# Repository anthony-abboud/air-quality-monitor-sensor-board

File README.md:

# AirQualityMonitor-SensorBoard (Pico2JSTboard)

Custom PCB for Lehigh University's Sustainable Engineering Club Air Quality Monitor project. Integrates a Raspberry Pi Pico 2 W with a Sensirion SEN54 environmental sensor for low-cost, IoT-connected indoor air quality monitoring.

## Overview

The original prototype connected the Pico 2 W to the SEN54 sensor via breadboard and loose cabling. This board replaces that setup with a compact, pluggable assembly: two socket headers accept the Pico 2 W directly, and an onboard JST connector interfaces with the SEN54 over a short cable, eliminating fragile wiring from the prototype.

## Components

| Part | Manufacturer | Notes |
|---|---|---|
| SEN54 | Sensirion | Environmental sensor node — PM, RH/T, VOC measurements |
| Raspberry Pi Pico 2 W (with headers) | Raspberry Pi | Wi-Fi–enabled microcontroller |
| 5V power supply (microUSB) | — | Powers the board via the Pico's VBUS |

## Wiring

| SEN54 Pin (JST GHR-06V-S) | Function | Pico 2 W Pin | Net |
|---|---|---|---|
| 1 | VDD | 40 (VBUS) | `VDD_5V` |
| 2 | GND | 3 (GND) | `GND` |
| 3 | SDA | 6 (GP4, I2C0 SDA) | `I2C0_SDA` |
| 4 | SCL | 7 (GP5, I2C0 SCL) | `I2C0_SCL` |
| 5 | SEL | 8 (GND) | `GND` — tied low to select I2C mode |
| 6 | NC | — | not connected |

## Schematic

## PCB Layout

## Design Notes

- Two socket headers, manually spaced to fit the Pico 2 W, replace the breadboard and loose cabling from the original prototype.
- The onboard JST connector interfaces with the SEN54 over a cable, keeping the sensor off-board for flexible mounting.
- The SEN54's SEL pin is tied to GND to select I2C communication mode (rather than UART).
- All ground connections (sensor GND, SEL, and Pico pin 3) share a single common `GND` net.

## Repository Structure

```
/hardware   KiCad project files (schematic, PCB layout, fabrication outputs)
/images     Rendered images used in this README
/firmware   Microcontroller code (in active development)
```

## Status

Board designed, fabricated, and assembled. Firmware is in active development.

## References

- [Raspberry Pi Pico 2 W Datasheet](https://datasheets.raspberrypi.com/picow/pico-2-w-datasheet.pdf)
- [Sensirion SEN5x Datasheet](https://sensirion.com/media/documents/6791EFA0/62A1F68F/Sensirion_Datasheet_Environmental_Node_SEN5x.pdf)

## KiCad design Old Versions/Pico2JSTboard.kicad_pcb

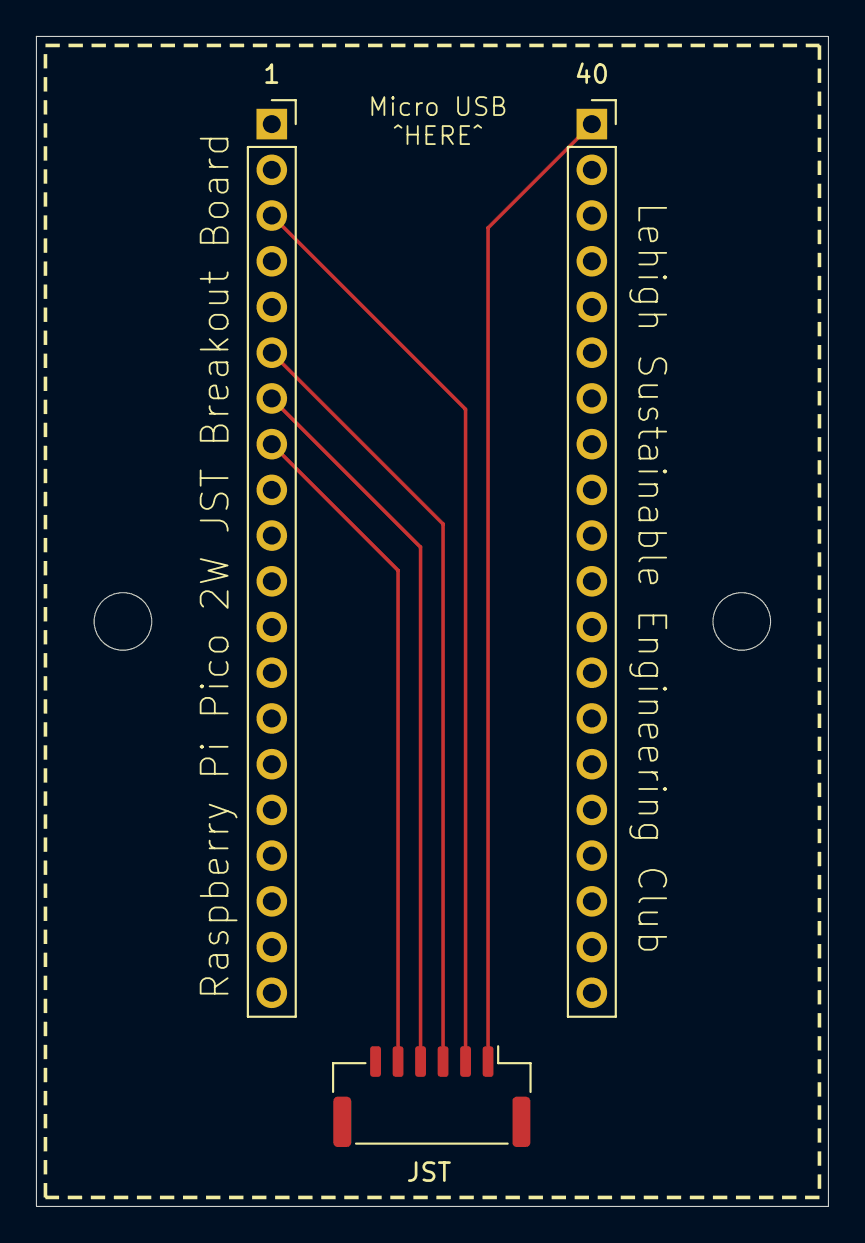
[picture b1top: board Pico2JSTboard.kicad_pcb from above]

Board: 2 copper layers, 44.0 x 65.0 mm, 3 parts (0 on the bottom side), 5 nets.

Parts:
1, 40: PinSocket_1x20_P2.54mm_Vertical
JST: JST_GH_BM06B-GHS-TBT_1x06-1MP_P1.25mm_Vertical

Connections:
Net1: 40.1, JST.1
Net2: 1.3, JST.2
Net3: 1.6, JST.3
Net4: 1.7, JST.4
Net5: 1.8, JST.5
